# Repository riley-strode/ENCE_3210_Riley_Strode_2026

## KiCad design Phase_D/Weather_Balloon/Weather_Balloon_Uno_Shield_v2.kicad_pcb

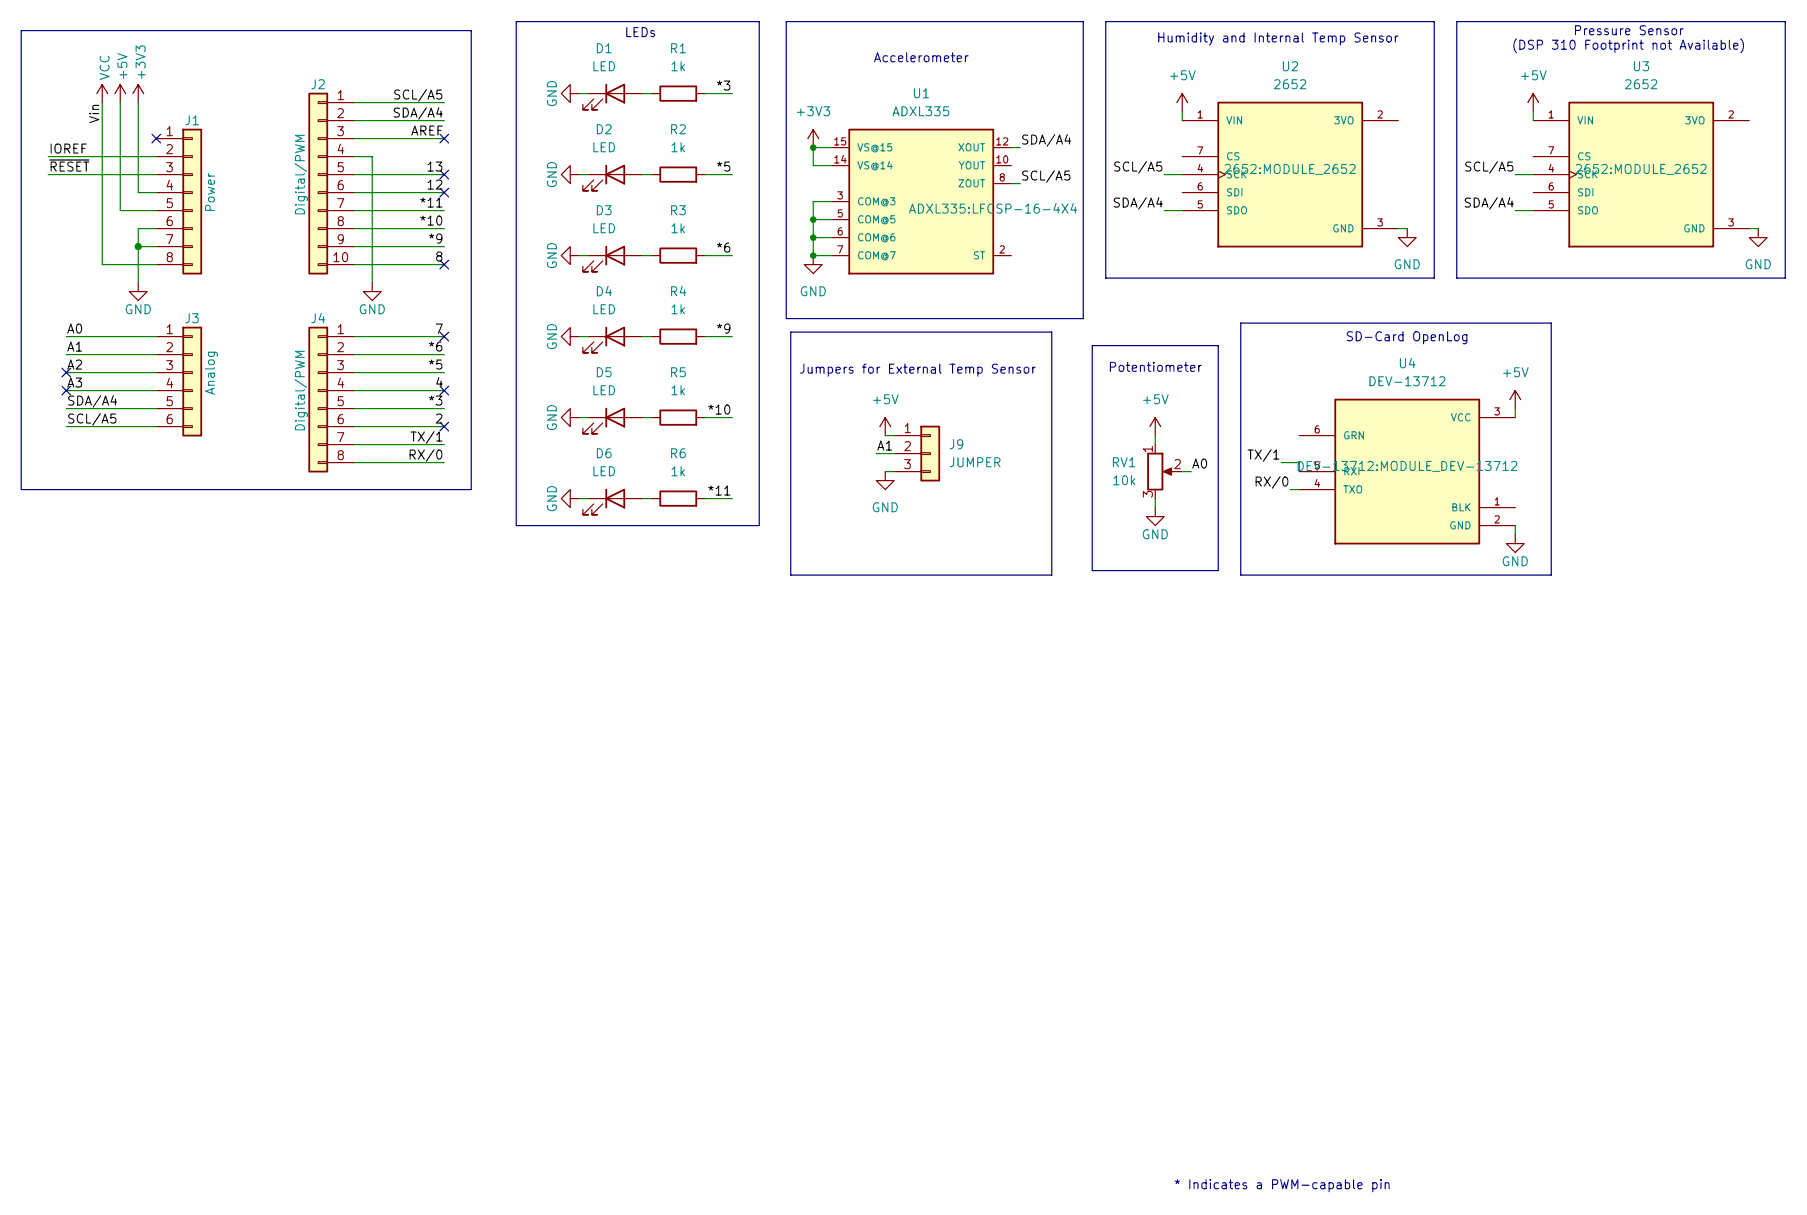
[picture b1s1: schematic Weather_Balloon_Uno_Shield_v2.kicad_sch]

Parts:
D1, D2, D3, D4, D5, D6: LED; LED_D5.0mm
J1: Power; PinSocket_1x08_P2.54mm_Vertical
J2: Digital/PWM; PinSocket_1x10_P2.54mm_Vertical
J3: Analog; PinSocket_1x06_P2.54mm_Vertical
J4: Digital/PWM; PinSocket_1x08_P2.54mm_Vertical
J9: JUMPER; PinHeader_1x03_P2.54mm_Vertical
R1, R2, R3, R4, R5, R6: 1k; R_Axial_DIN0207_L6.3mm_D2.5mm_P7.62mm_Horizontal
RV1: 10k; Potentiometer_Bourns_3386P_Vertical
U1: ADXL335; LFCSP-16-4X4
U2, U3: 2652; MODULE_2652; PARTREV N/A
U4: DEV-13712; MODULE_DEV-13712; PARTREV v15

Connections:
+3V3: J1.4, U1.14 (VS@14), U1.15 (VS@15)
+5V: J1.5, J9.1, RV1.1, U2.1 (VIN), U3.1 (VIN), U4.3 (VCC)
/2: J4.6
/4: J4.4
/7: J4.1
/8: J2.10
/12: J2.6
/13: J2.5
/*3: J4.5, R1.2
/*5: J4.3, R2.2
/*6: J4.2, R3.2
/*9: J2.9, R4.2
/*10: J2.8, R5.2
/*11: J2.7, R6.2
/A0: J3.1, RV1.2
/A1: J3.2, J9.2
/A2: J3.3
/A3: J3.4
/AREF: J2.3
/IOREF: J1.2
/RX/0: J4.8, U4.4 (TXO)
/SCL/A5: J2.1, J3.6, U1.8 (ZOUT), U2.4 (SCK), U3.4 (SCK)
/SDA/A4: J2.2, J3.5, U1.12 (XOUT), U2.5 (SDO), U3.5 (SDO)
/TX/1: J4.7, U4.5 (RXI)
/~RESET: J1.3
GND: D1.1 (K), D2.1 (K), D3.1 (K), D4.1 (K), D5.1 (K), D6.1 (K), J1.6, J1.7, J2.4, J9.3, RV1.3, U1.3 (COM@3), U1.5 (COM@5), U1.6 (COM@6), U1.7 (COM@7), U2.3 (GND), U3.3 (GND), U4.2 (GND)
unnamed: D1.2 (A), R1.1
unnamed: D2.2 (A), R2.1
unnamed: D3.2 (A), R3.1
unnamed: D4.2 (A), R4.1
unnamed: D5.2 (A), R5.1
unnamed: D6.2 (A), R6.1
VCC: J1.8

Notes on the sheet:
SD-Card OpenLog
Potentiometer
LEDs
Pressure Sensor (DSP 310 Footprint not Available)
Accelerometer
Humidity and Internal Temp Sensor
Jumpers for External Temp Sensor
* Indicates a PWM-capable pin

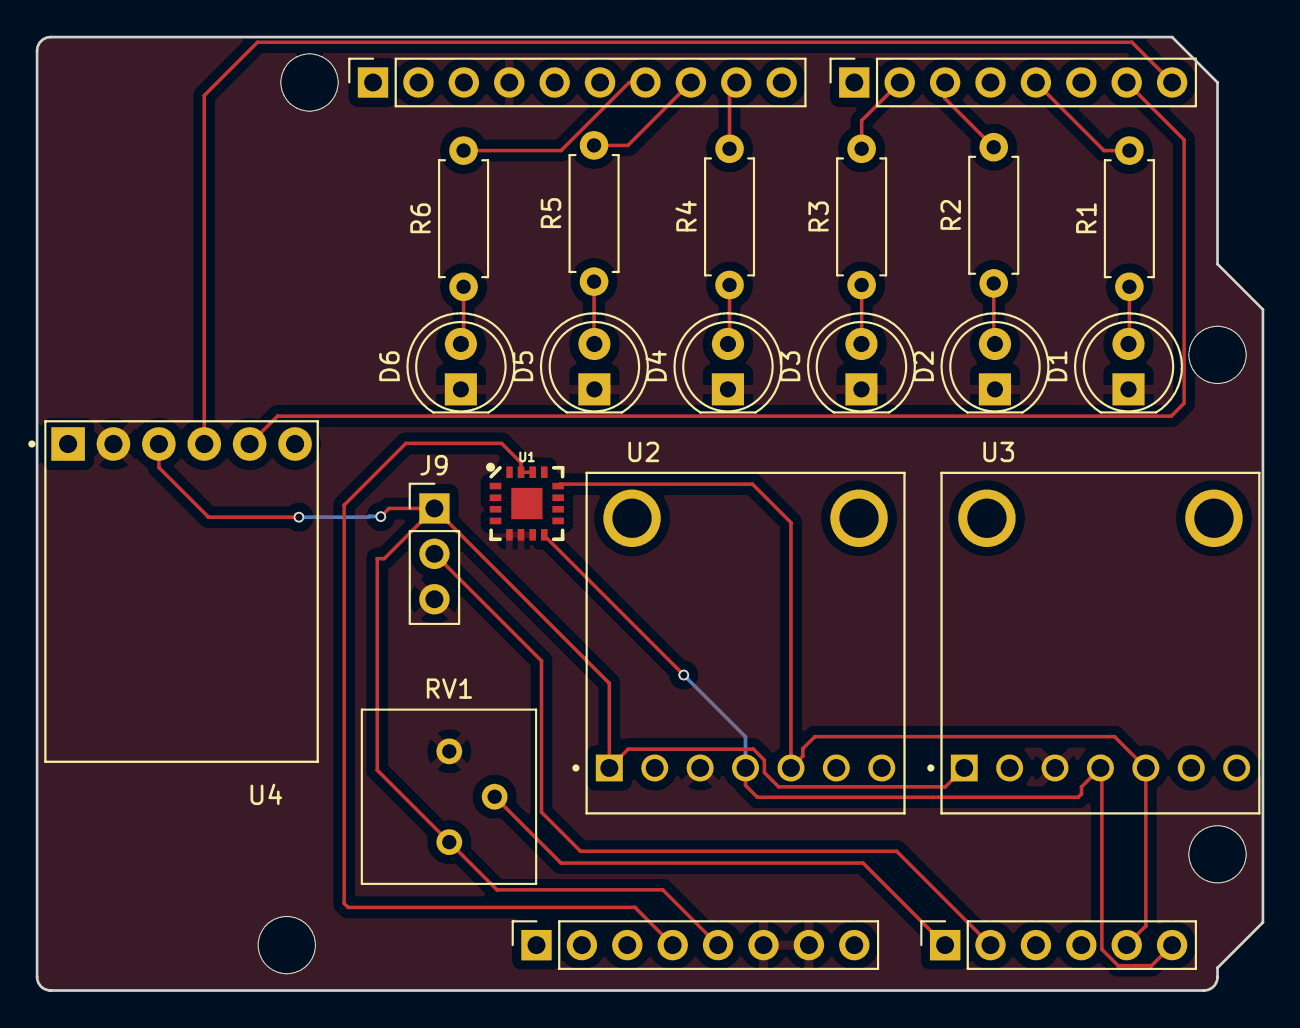
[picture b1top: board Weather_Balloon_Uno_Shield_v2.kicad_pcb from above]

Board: 2 copper layers, 68.6 x 53.3 mm, 26 parts (0 on the bottom side), 21 nets.

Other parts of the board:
MH1, MH2, MH3, MH4: MountingHole_3.2mm

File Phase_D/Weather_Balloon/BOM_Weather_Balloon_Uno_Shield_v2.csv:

"Id";"Designator";"Footprint";"Quantity";"Designation";"Supplier and ref";
1;"J1";"PinSocket_1x08_P2.54mm_Vertical";1;"Power";;;
2;"J3";"PinSocket_1x06_P2.54mm_Vertical";1;"Analog";;;
3;"J2";"PinSocket_1x10_P2.54mm_Vertical";1;"Digital/PWM";;;
4;"J4";"PinSocket_1x08_P2.54mm_Vertical";1;"Digital/PWM";;;
5;"D4,D5,D2,D3,D6,D1";"LED_D5.0mm";6;"LED";;;
6;"R1,R6,R3,R4,R2,R5";"R_Axial_DIN0207_L6.3mm_D2.5mm_P7.62mm_Horizontal";6;"1k";;;
7;"U4";"MODULE_DEV-13712";1;"DEV-13712";;;
8;"U3,U2";"MODULE_2652";2;"2652";;;
9;"RV1";"Potentiometer_Bourns_3386P_Vertical";1;"10k";;;
10;"J9";"PinHeader_1x03_P2.54mm_Vertical";1;"JUMPER";;;
11;"U1";"LFCSP-16-4X4";1;"ADXL335";;;

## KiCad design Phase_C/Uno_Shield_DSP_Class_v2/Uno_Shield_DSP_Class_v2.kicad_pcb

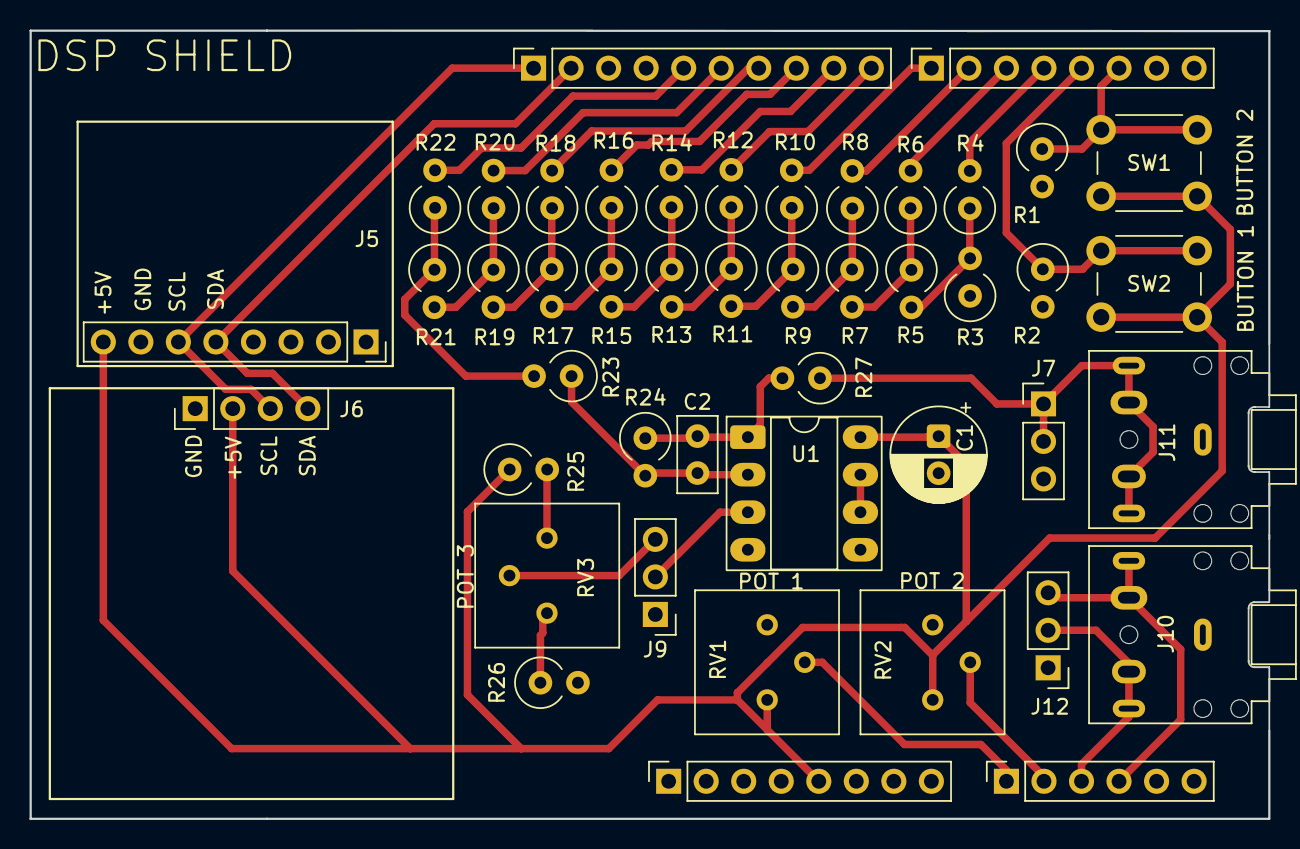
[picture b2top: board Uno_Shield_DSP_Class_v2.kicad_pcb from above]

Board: 2 copper layers, 83.8 x 53.3 mm, 46 parts (0 on the bottom side), 38 nets.

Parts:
C1: 47uF; CP_Radial_D6.3mm_P2.50mm
C2: 100pF; C_Disc_D5.0mm_W2.5mm_P2.50mm
J1: Power; PinSocket_1x08_P2.54mm_Vertical
J2: Digital/PWM; PinSocket_1x10_P2.54mm_Vertical
J3: Analog; PinSocket_1x06_P2.54mm_Vertical
J4: Digital/PWM; PinSocket_1x08_P2.54mm_Vertical
J5: IMU_CONN; PinSocket_1x08_P2.54mm_Vertical
J6: SCREEN_CONN; PinHeader_1x04_P2.54mm_Vertical
J7: AUDIO_OUT; PinHeader_1x03_P2.54mm_Vertical
J9: JUMPER; PinHeader_1x03_P2.54mm_Vertical
J10, J11: AudioJack5; Jack_3.5mm_CUI_SJ1-3525N_Horizontal
J12: AUDIO_IN; PinHeader_1x03_P2.54mm_Vertical
R1, R2: 100k; R_Axial_DIN0309_L9.0mm_D3.2mm_P2.54mm_Vertical
R3, R4, R6, R8, R10, R12, R14, R16, R18, R20, R22, R23, R24, R25, R26: 20k; R_Axial_DIN0309_L9.0mm_D3.2mm_P2.54mm_Vertical
R5, R7, R9, R11, R13, R15, R17, R19, R21: 10k; R_Axial_DIN0309_L9.0mm_D3.2mm_P2.54mm_Vertical
R27: 1k; R_Axial_DIN0309_L9.0mm_D3.2mm_P2.54mm_Vertical
RV1, RV2, RV3: 100k; Potentiometer_Bourns_3386P_Vertical
SW1: BT_1; SW_PUSH_6mm
SW2: BT_2; SW_PUSH_6mm
U1: MCP6002-xP; DIP-8_W7.62mm_Socket_LongPads

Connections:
+5V: C1.1, J1.5, J5.8, J6.2, R25.1, RV1.1, RV2.1, SW1.1, SW2.1, U1.8 (V+)
/A0: J3.1, RV1.2
/A1: J3.2, RV2.2
/AUDIO_OUT: J7.1, J7.2, J11.R, J11.RN, J11.T, J11.TN, R27.1
/BT1: J4.6, R1.1, SW1.2
/BT2: J4.5, R2.1, SW2.2
/D0: J4.4, R4.2
/D1: J4.3, R6.2
/D2: J4.2, R8.2
/D3: J4.1, R10.2
/D4: J2.10, R12.2
/D5: J2.9, R14.2
/D6: J2.8, R16.2
/D7: J2.7, R18.2
/D8: J2.6, R20.2
/D9: J2.5, R22.2
/IN_LEFT: J3.4, J10.T, J10.TN, J12.3
/IN_RIGHT: J3.3, J10.R, J10.RN, J12.2
/SCL: J2.1, J5.6, J6.3
/SDA: J2.2, J5.5, J6.4
GND: C1.2, J1.6, J1.7, J2.4, J5.7, J6.1, J7.3, J9.1, J10.S, J11.S, J12.1, R1.2, R2.2, R3.1, R26.2, RV1.3, RV2.3, U1.4 (V-), U1.5 (+)
unnamed: C2.2, R24.1, R27.2, U1.1
unnamed: J9.2, U1.3 (+)
unnamed: J9.3, RV3.2
unnamed: R3.2, R4.1, R5.2
unnamed: R5.1, R6.1, R7.2
unnamed: R7.1, R8.1, R9.2
unnamed: R9.1, R10.1, R11.2
unnamed: R11.1, R12.1, R13.2
unnamed: R13.1, R14.1, R15.2
unnamed: R15.1, R16.1, R17.2
unnamed: R17.1, R18.1, R19.2
unnamed: R19.1, R20.1, R21.2
unnamed: R21.1, R22.1, R23.2
unnamed: R25.2, RV3.1
unnamed: R26.1, RV3.3
unnamed: C2.1, R23.1, R24.2, U1.2 (-)
unnamed: U1.6 (-), U1.7

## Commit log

2026-01-30 Create temp
2026-02-04 Create temp3
2026-02-05 Create Temp4
2026-02-16 Create Temp_5
2026-03-09 Create PlaceholderC
2026-03-13 Create tester6
